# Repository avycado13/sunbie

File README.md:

# Sunbie
a starbie but kinda in the shape of the sun.

## Features
- 1 Inch Display
- 3 Sensors all communicating over I2C
- LSM6DS3 for IMU and motion detection
- BME280 for temperature and environment detection
- TSL25911FN for light detection that I will probably hook up to control screen brightness
- 2 Multicolor addressable LEDs (WS2812B)
- 5 Buttons
- Buzzer that can generate multiple pitches
- Testpoints for easy debugging
- Optional Battery Soldering point
- Powered by XIAO ESP32-C3

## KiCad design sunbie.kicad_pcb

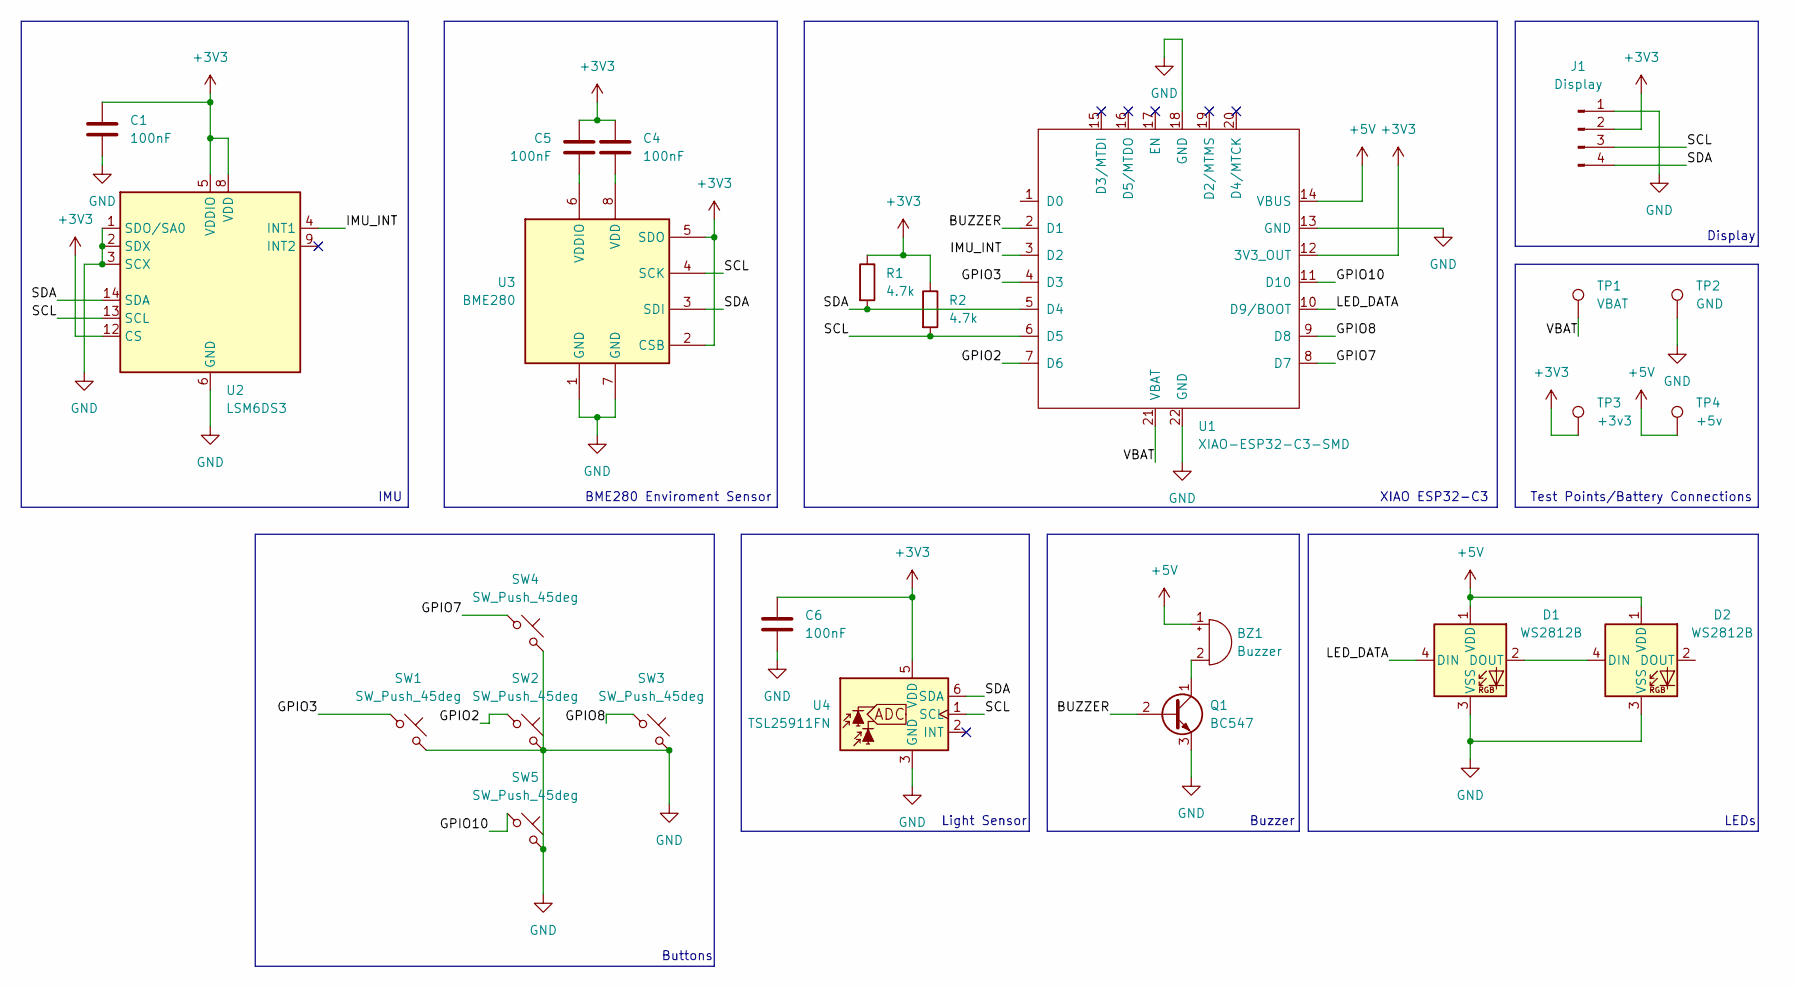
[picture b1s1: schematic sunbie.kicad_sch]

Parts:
BZ1: Buzzer; Buzzer_Murata_PKLCS1212E
C1, C4, C5, C6: 100nF; C_0805_2012Metric_Pad1.18x1.45mm_HandSolder
D1, D2: WS2812B; LED_WS2812B_PLCC4_5.0x5.0mm_P3.2mm
J1: Display; Display_128x64_096_I2C
Q1: BC547; TO-92_Inline
R1, R2: 4.7k; R_0805_2012Metric_Pad1.20x1.40mm_HandSolder
SW1, SW2, SW3, SW4, SW5: SW_Push_45deg; SW_PUSH_6mm
TP1: VBAT; TestPoint_Pad_D4.0mm
TP2: GND; TestPoint_Pad_D4.0mm
TP3: +3v3; TestPoint_Pad_D4.0mm
TP4: +5v; TestPoint_Pad_D4.0mm
U1: XIAO-ESP32-C3-SMD
U2: LSM6DS3; LGA-14_3x2.5mm_P0.5mm_LayoutBorder3x4y
U3: BME280; Bosch_LGA-8_2.5x2.5mm_P0.65mm_ClockwisePinNumbering
U4: TSL25911FN; AMS_TSL25911FN

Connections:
+3V3: C1.1, C4.1, C5.1, C6.1, J1.2, R1.1, R2.1, TP3.1 (1_1), U1.12 (3V3_OUT), U2.5 (VDDIO), U2.8 (VDD), U2.12 (CS), U3.2 (CSB), U3.5 (SDO), U4.5 (VDD)
+5V: BZ1.1 (+), D1.1 (VDD), D2.1 (VDD), TP4.1 (1_1), U1.14 (VBUS)
/BUZZER: Q1.2 (B), U1.2 (D1)
/GPIO2: SW2.1, U1.7 (D6)
/GPIO3: SW1.1, U1.4 (D3)
/GPIO7: SW4.1, U1.8 (D7)
/GPIO8: SW3.1, U1.9 (D8)
/GPIO10: SW5.1, U1.11 (D10)
/IMU_INT: U1.3 (D2), U2.4 (INT1)
/LED_DATA: D1.4 (DIN), U1.10 (D9/BOOT)
/SCL: J1.3, R2.2, U1.6 (D5), U2.13 (SCL), U3.4 (SCK), U4.1 (SCL)
/SDA: J1.4, R1.2, U1.5 (D4), U2.14 (SDA), U3.3 (SDI), U4.6 (SDA)
/VBAT: TP1.1 (1_1), U1.21 (VBAT)
GND: C1.2, C6.2, D1.3 (VSS), D2.3 (VSS), J1.1, Q1.3 (E), SW1.2, SW2.2, SW3.2, SW4.2, SW5.2, TP2.1 (1_1), U1.13 (GND), U1.18 (GND), U1.22 (GND), U2.1 (SDO/SA0), U2.2 (SDX), U2.3 (SCX), U2.6 (GND), U2.7 (GND), U3.1 (GND), U3.7 (GND), U4.3 (GND)
unnamed: BZ1.2 (-), Q1.1 (C)
unnamed: D1.2 (DOUT), D2.4 (DIN)
unnamed: C4.2, U3.8 (VDD)
unnamed: C5.2, U3.6 (VDDIO)

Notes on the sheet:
Buttons
XIAO ESP32-C3
IMU
Buzzer
Display
LEDs
BME280 Enviroment Sensor
Test Points/Battery Connections
Light Sensor

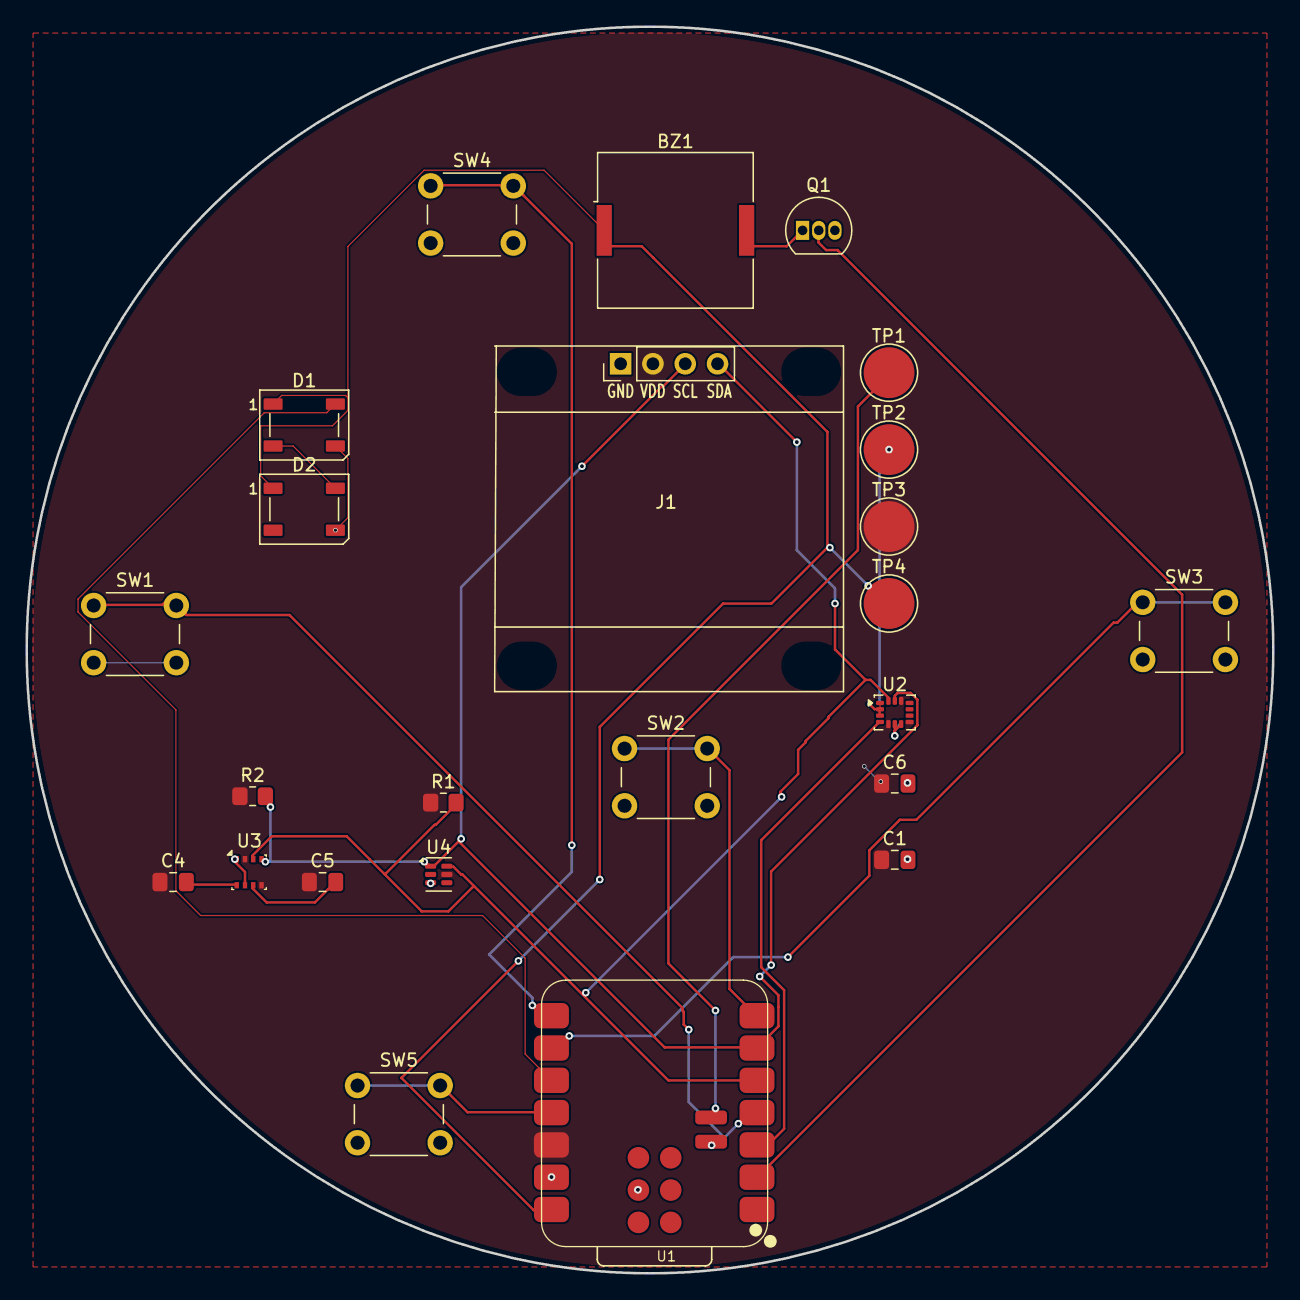
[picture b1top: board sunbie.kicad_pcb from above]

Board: 2 copper layers, 98.0 x 98.0 mm, 24 parts (0 on the bottom side), 18 nets.

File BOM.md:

# Starbie – bill of materials

<!-- Generated by Half Life from project cmuvw0qc6027b01osx23dl5bq. Edits here are overwritten on the next sync. -->
<!-- Generated: 2026-10-10T18:27:59.264Z -->

> [!NOTE]
> This parts list is mirrored from [Half Life](https://halflife.hackclub.com). Editing it here will not change the platform's copy, and the next sync overwrites this file.

| Week | Tier | Parts funding |
| --- | --- | --- |
| Week 1 | Tier 1 | $30.00 |

| Part | What it's for | Qty | Unit | Total | Vendor |
| --- | --- | --- | --- | --- | --- |
| [Seeed Studio XIAO ESP32-C3](https://www.seeedstudio.com/Seeed-XIAO-ESP32C3-p-5431.html) | Main Microcontroller | 1 | $4.99 | $4.99 | [Seeed Studios](https://www.seeedstudio.com/Seeed-XIAO-ESP32C3-p-5431.html) |
| [Bosch BME280](https://www.lcsc.com/product-detail/C92489.html) | Temperature and atmosphere detection | 1 | $7.71 | $7.71 | [LCSC](https://www.lcsc.com/product-detail/C92489.html) |
| [LSM6DS3TR-C](https://www.lcsc.com/product-detail/C967633.html) | IMU for motion detection | 1 | $1.53 | $1.53 | [LCSC](https://www.lcsc.com/product-detail/C967633.html) |
| [Worldsemi WS2812B-V5/W](https://www.lcsc.com/product-detail/C2874885.html) | LEDs for signalling to user without display | 5 | $0.11 | $0.55 | [LCSC](https://www.lcsc.com/product-detail/C2874885.html) |
| [OSRAM TSL25911FN](https://www.lcsc.com/product-detail/C22459879.html) | Light sensor for display brightness and sleep animations | 1 | $2.82 | $2.82 | [LCSC](https://www.lcsc.com/product-detail/C22459879.html) |
| [BC547](https://www.lcsc.com/product-detail/C50229581.html) | Transistor for controlling piezo. I need 50 because of lcsc | 50 | $0.01 | $0.50 | [LCSC](https://www.lcsc.com/product-detail/C50229581.html) |
| [muRata PKLCS1212E4001-R1](https://www.lcsc.com/product-detail/C113159.html) | Buzzer Piezo to make cool sounds | 1 | $0.80 | $0.80 | [LCSC](https://www.lcsc.com/product-detail/C113159.html) |
| [kinghelm KH-6X6X5H-TJ](https://www.lcsc.com/product-detail/C2837515.html) | 6mm Push Buttons for User Control | 1 | $0.02 | $0.02 | [LCSC](https://www.lcsc.com/product-detail/C2837515.html) |
| [Display](https://www.amazon.com/dp/B0GBWXTR1Z?) | Display for showing animations and details | 1 | $5.99 | $5.99 | [Amazon](https://www.amazon.com/dp/B0GBWXTR1Z?) |
| **Parts subtotal** | — | — | — | **$24.91** | — |
| **Tax & shipping** | — | — | — | **$0.00** | — |
| **Total** | — | — | — | **$24.91** | — |

$5.09 left of the tier's funding.
